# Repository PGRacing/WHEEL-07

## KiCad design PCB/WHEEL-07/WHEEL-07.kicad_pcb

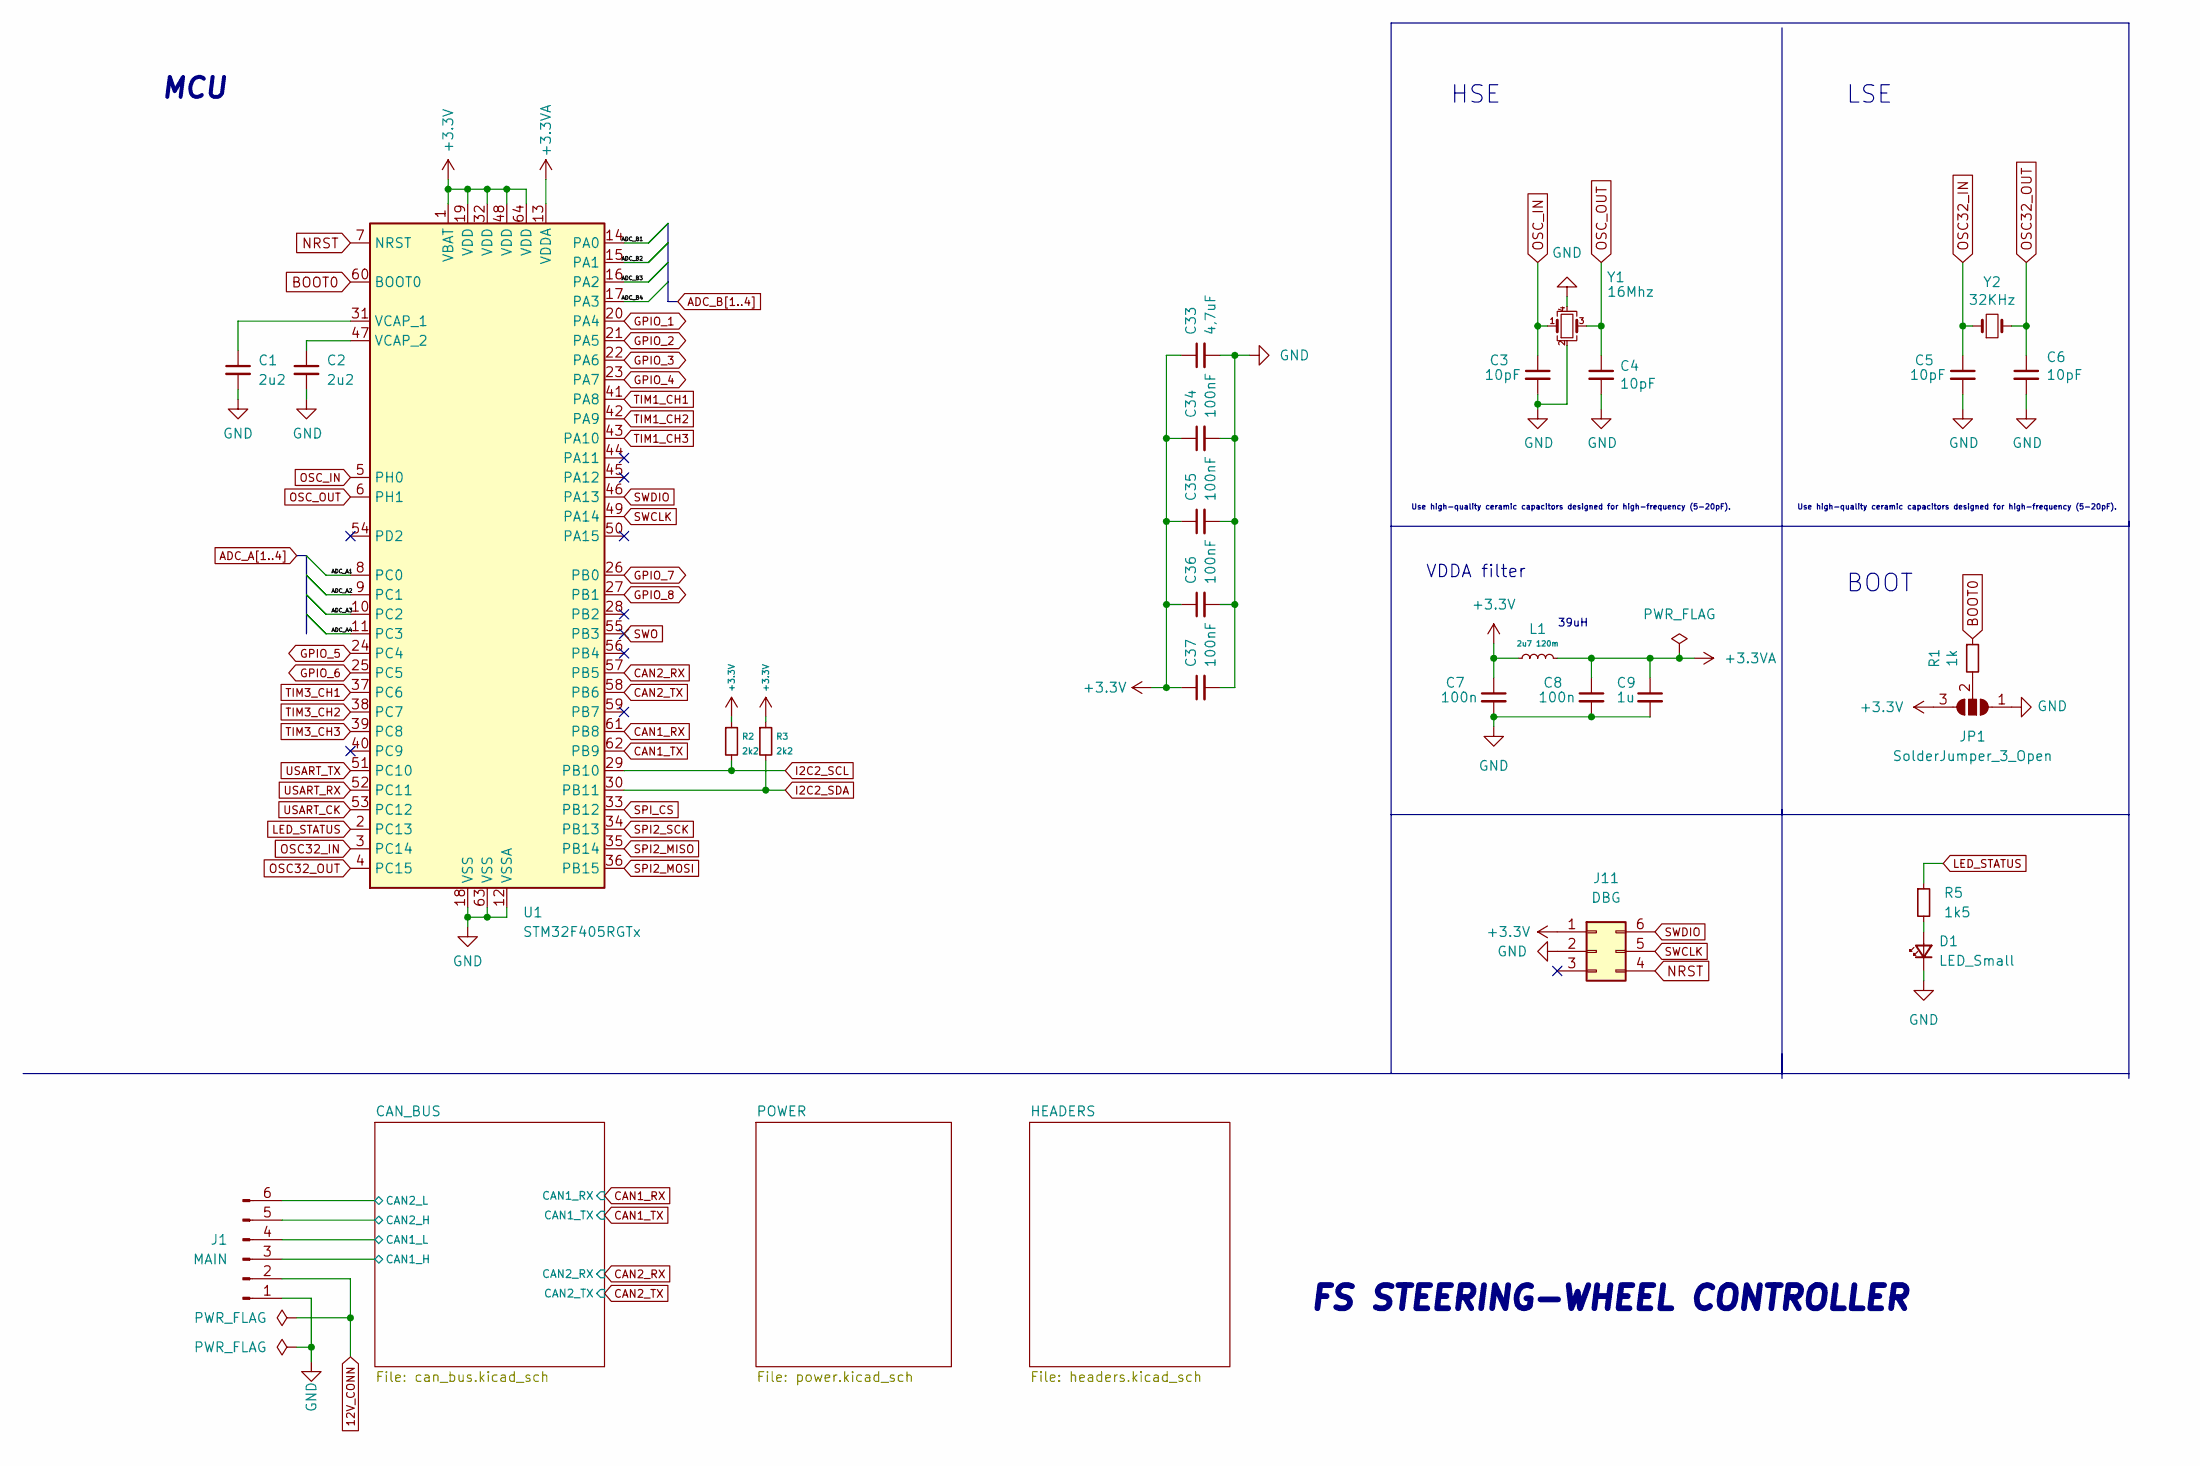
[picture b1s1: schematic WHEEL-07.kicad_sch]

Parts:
C1, C2: 2u2; C_0402_1005Metric_Pad0.74x0.62mm_HandSolder
C3, C4, C5, C6: 10pF; C_0402_1005Metric_Pad0.74x0.62mm_HandSolder
C7, C8: 100n; C_0402_1005Metric_Pad0.74x0.62mm_HandSolder
C9: 1u; C_0402_1005Metric_Pad0.74x0.62mm_HandSolder
C33: 4,7uF; C_0603_1608Metric
C34, C35, C36, C37: 100nF; C_0402_1005Metric_Pad0.74x0.62mm_HandSolder
D1: LED_Small; LED_0805_2012Metric
J1: MAIN; Molex_Micro-Latch_53254-0670_1x06_P2.00mm_Horizontal
J11: DBG; PinHeader_2x03_P1.27mm_Vertical
JP1: SolderJumper_3_Open; SolderJumper-3_P1.3mm_Open_RoundedPad1.0x1.5mm
L1: 2u7 120m; L_0402_1005Metric
R1: 1k; R_0402_1005Metric_Pad0.72x0.64mm_HandSolder
R2, R3: 2k2; R_0402_1005Metric_Pad0.72x0.64mm_HandSolder
R5: 1k5; R_0402_1005Metric_Pad0.72x0.64mm_HandSolder
U1: STM32F405RGTx; LQFP-64_10x10mm_P0.5mm
Y1: 16Mhz; Crystal_SMD_2016-4Pin_2.0x1.6mm
Y2: 32KHz; Crystal_SMD_3215-2Pin_3.2x1.5mm

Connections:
12V_CONN: J1.2; also elsewhere on the board
+3.3V: C7.1, C33.1, C34.1, C35.1, C36.1, C37.1, J11.1, JP1.3 (B), L1.1, R2.1, R3.1, U1.1 (VBAT), U1.19 (VDD), U1.32 (VDD), U1.48 (VDD), U1.64 (VDD); also elsewhere on the board
+3.3VA: C8.1, C9.1, L1.2, U1.13 (VDDA)
/CAN_BUS/CAN1_H: J1.3; also elsewhere on the board
/CAN_BUS/CAN1_L: J1.4; also elsewhere on the board
/CAN_BUS/CAN2_H: J1.5; also elsewhere on the board
/CAN_BUS/CAN2_L: J1.6; also elsewhere on the board
ADC_A1: U1.8 (PC0); also elsewhere on the board
ADC_A2: U1.9 (PC1); also elsewhere on the board
ADC_A3: U1.10 (PC2); also elsewhere on the board
ADC_A4: U1.11 (PC3); also elsewhere on the board
ADC_B1: U1.14 (PA0); also elsewhere on the board
ADC_B2: U1.15 (PA1); also elsewhere on the board
ADC_B3: U1.16 (PA2); also elsewhere on the board
ADC_B4: U1.17 (PA3); also elsewhere on the board
BOOT0: R1.1, U1.60 (BOOT0)
CAN1_RX: U1.61 (PB8); also elsewhere on the board
CAN1_TX: U1.62 (PB9); also elsewhere on the board
CAN2_RX: U1.57 (PB5); also elsewhere on the board
CAN2_TX: U1.58 (PB6); also elsewhere on the board
GND: C1.2, C2.2, C3.2, C4.2, C5.2, C6.2, C7.2, C8.2, C9.2, C33.2, C34.2, C35.2, C36.2, C37.2, D1.1 (K), J1.1, J11.2, JP1.1 (A), U1.12 (VSSA), U1.18 (VSS), U1.63 (VSS), Y1.2, Y1.4; also elsewhere on the board
GPIO_1: U1.20 (PA4); also elsewhere on the board
GPIO_2: U1.21 (PA5); also elsewhere on the board
GPIO_3: U1.22 (PA6); also elsewhere on the board
GPIO_4: U1.23 (PA7); also elsewhere on the board
GPIO_5: U1.24 (PC4); also elsewhere on the board
GPIO_6: U1.25 (PC5); also elsewhere on the board
GPIO_7: U1.26 (PB0); also elsewhere on the board
GPIO_8: U1.27 (PB1); also elsewhere on the board
I2C2_SCL: R2.2, U1.29 (PB10); also elsewhere on the board
I2C2_SDA: R3.2, U1.30 (PB11); also elsewhere on the board
LED_STATUS: R5.1, U1.2 (PC13)
NRST: J11.4, U1.7 (NRST)
unnamed: C1.1, U1.31 (VCAP_1)
unnamed: C2.1, U1.47 (VCAP_2)
unnamed: D1.2 (A), R5.2
unnamed: JP1.2 (C), R1.2
OSC32_IN: C5.1, U1.3 (PC14), Y2.1
OSC32_OUT: C6.1, U1.4 (PC15), Y2.2
OSC_IN: C3.1, U1.5 (PH0), Y1.1
OSC_OUT: C4.1, U1.6 (PH1), Y1.3
SPI2_MISO: U1.35 (PB14); also elsewhere on the board
SPI2_MOSI: U1.36 (PB15); also elsewhere on the board
SPI2_SCK: U1.34 (PB13); also elsewhere on the board
SPI_CS: U1.33 (PB12); also elsewhere on the board
SWCLK: J11.5, U1.49 (PA14)
SWDIO: J11.6, U1.46 (PA13)
SWO: U1.55 (PB3)
TIM1_CH1: U1.41 (PA8); also elsewhere on the board
TIM1_CH2: U1.42 (PA9); also elsewhere on the board
TIM1_CH3: U1.43 (PA10); also elsewhere on the board
TIM3_CH1: U1.37 (PC6); also elsewhere on the board
TIM3_CH2: U1.38 (PC7); also elsewhere on the board
TIM3_CH3: U1.39 (PC8); also elsewhere on the board
USART_CK: U1.53 (PC12)
USART_RX: U1.52 (PC11)
USART_TX: U1.51 (PC10)

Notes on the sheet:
39uH
LSE
MCU
BOOT
Use high-quality ceramic capacitors designed for high-frequency (5-20pF).
HSE
VDDA filter
FS STEERING-WHEEL CONTROLLER

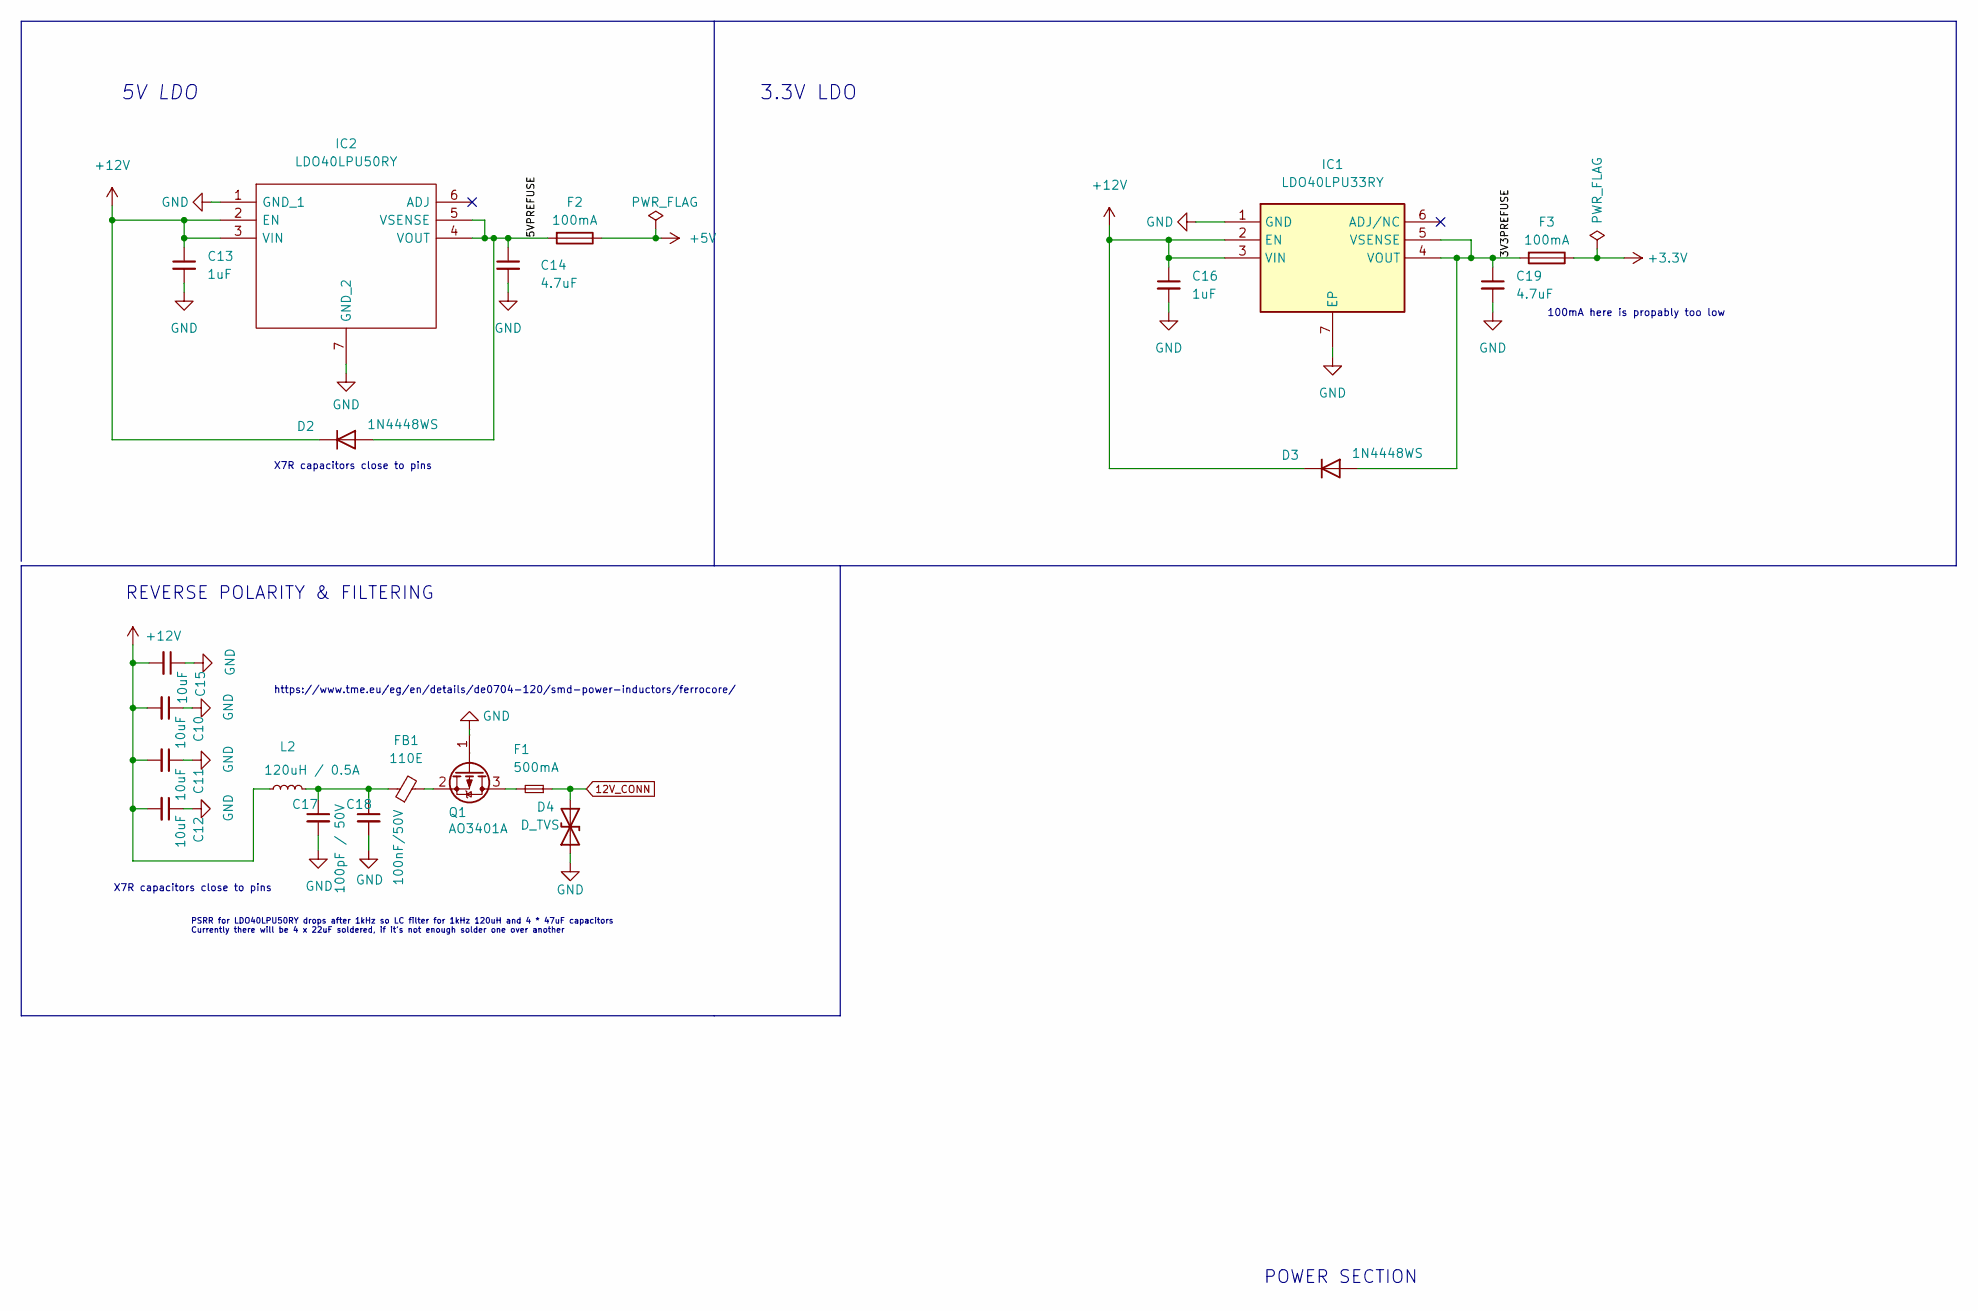
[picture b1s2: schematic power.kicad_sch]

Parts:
C10, C11, C12, C15: 10uF; C_1206_3216Metric
C13, C16: 1uF; C_0805_2012Metric
C14, C19: 4.7uF; C_0603_1608Metric
C17: 100pF / 50V; C_0402_1005Metric
C18: 100nF/50V; C_0402_1005Metric
D2, D3: 1N4448WS; D_SOD-323
D4: D_TVS; D_SMA
F1: 500mA; Fuse_0805_2012Metric
F2, F3: 100mA; Fuse_0805_2012Metric
FB1: 110E; LED_0805_2012Metric
IC1: LDO40LPU33RY; SON95P300X300X90-7N-D; Manufacturer_Part_Number LDO40LPU33RY; Mouser Part Number 511-LDO40LPU33RY
IC2: LDO40LPU50RY; SON95P300X300X90-7N-D; Manufacturer_Part_Number LDO40LPU50RY; Mouser Part Number 511-LDO40LPU50RY
L2: 120uH / 0.5A; L_7.3x7.3_H4.5
Q1: AO3401A; SOT-23

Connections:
12V_CONN: D4.2 (A2), F1.1; also elsewhere on the board
+3.3V: F3.1; also elsewhere on the board
+5V: F2.1; also elsewhere on the board
+12V: C10.2, C11.2, C12.2, C13.1, C15.2, C16.1, D2.1 (K), D3.1 (K), IC1.2 (EN), IC1.3 (VIN), IC2.2 (EN), IC2.3 (VIN), L2.1
/POWER/3V3PREFUSE: C19.1, D3.2 (A), F3.2, IC1.4 (VOUT), IC1.5 (VSENSE)
/POWER/5VPREFUSE: C14.1, D2.2 (A), F2.2, IC2.4 (VOUT), IC2.5 (VSENSE)
GND: C10.1, C11.1, C12.1, C13.2, C14.2, C15.1, C16.2, C17.2, C18.2, C19.2, D4.1 (A1), IC1.1 (GND), IC1.7 (EP), IC2.1 (GND_1), IC2.7 (GND_2), Q1.1 (G); also elsewhere on the board
unnamed: C17.1, C18.1, FB1.1, L2.2
unnamed: F1.2, Q1.3 (D)
unnamed: FB1.2, Q1.2 (S)

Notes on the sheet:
X7R capacitors close to pins
POWER SECTION
100mA here is propably too low
PSRR for LDO40LPU50RY drops after 1kHz so LC filter for 1kHz 120uH and 4 * 47uF capacitors Currently there will be 4 x 22uF soldered, if it's not enough solder one over another
https://www.tme.eu/eg/en/details/de0704-120/smd-power-inductors/ferrocore/
3.3V LDO
5V LDO
REVERSE POLARITY & FILTERING

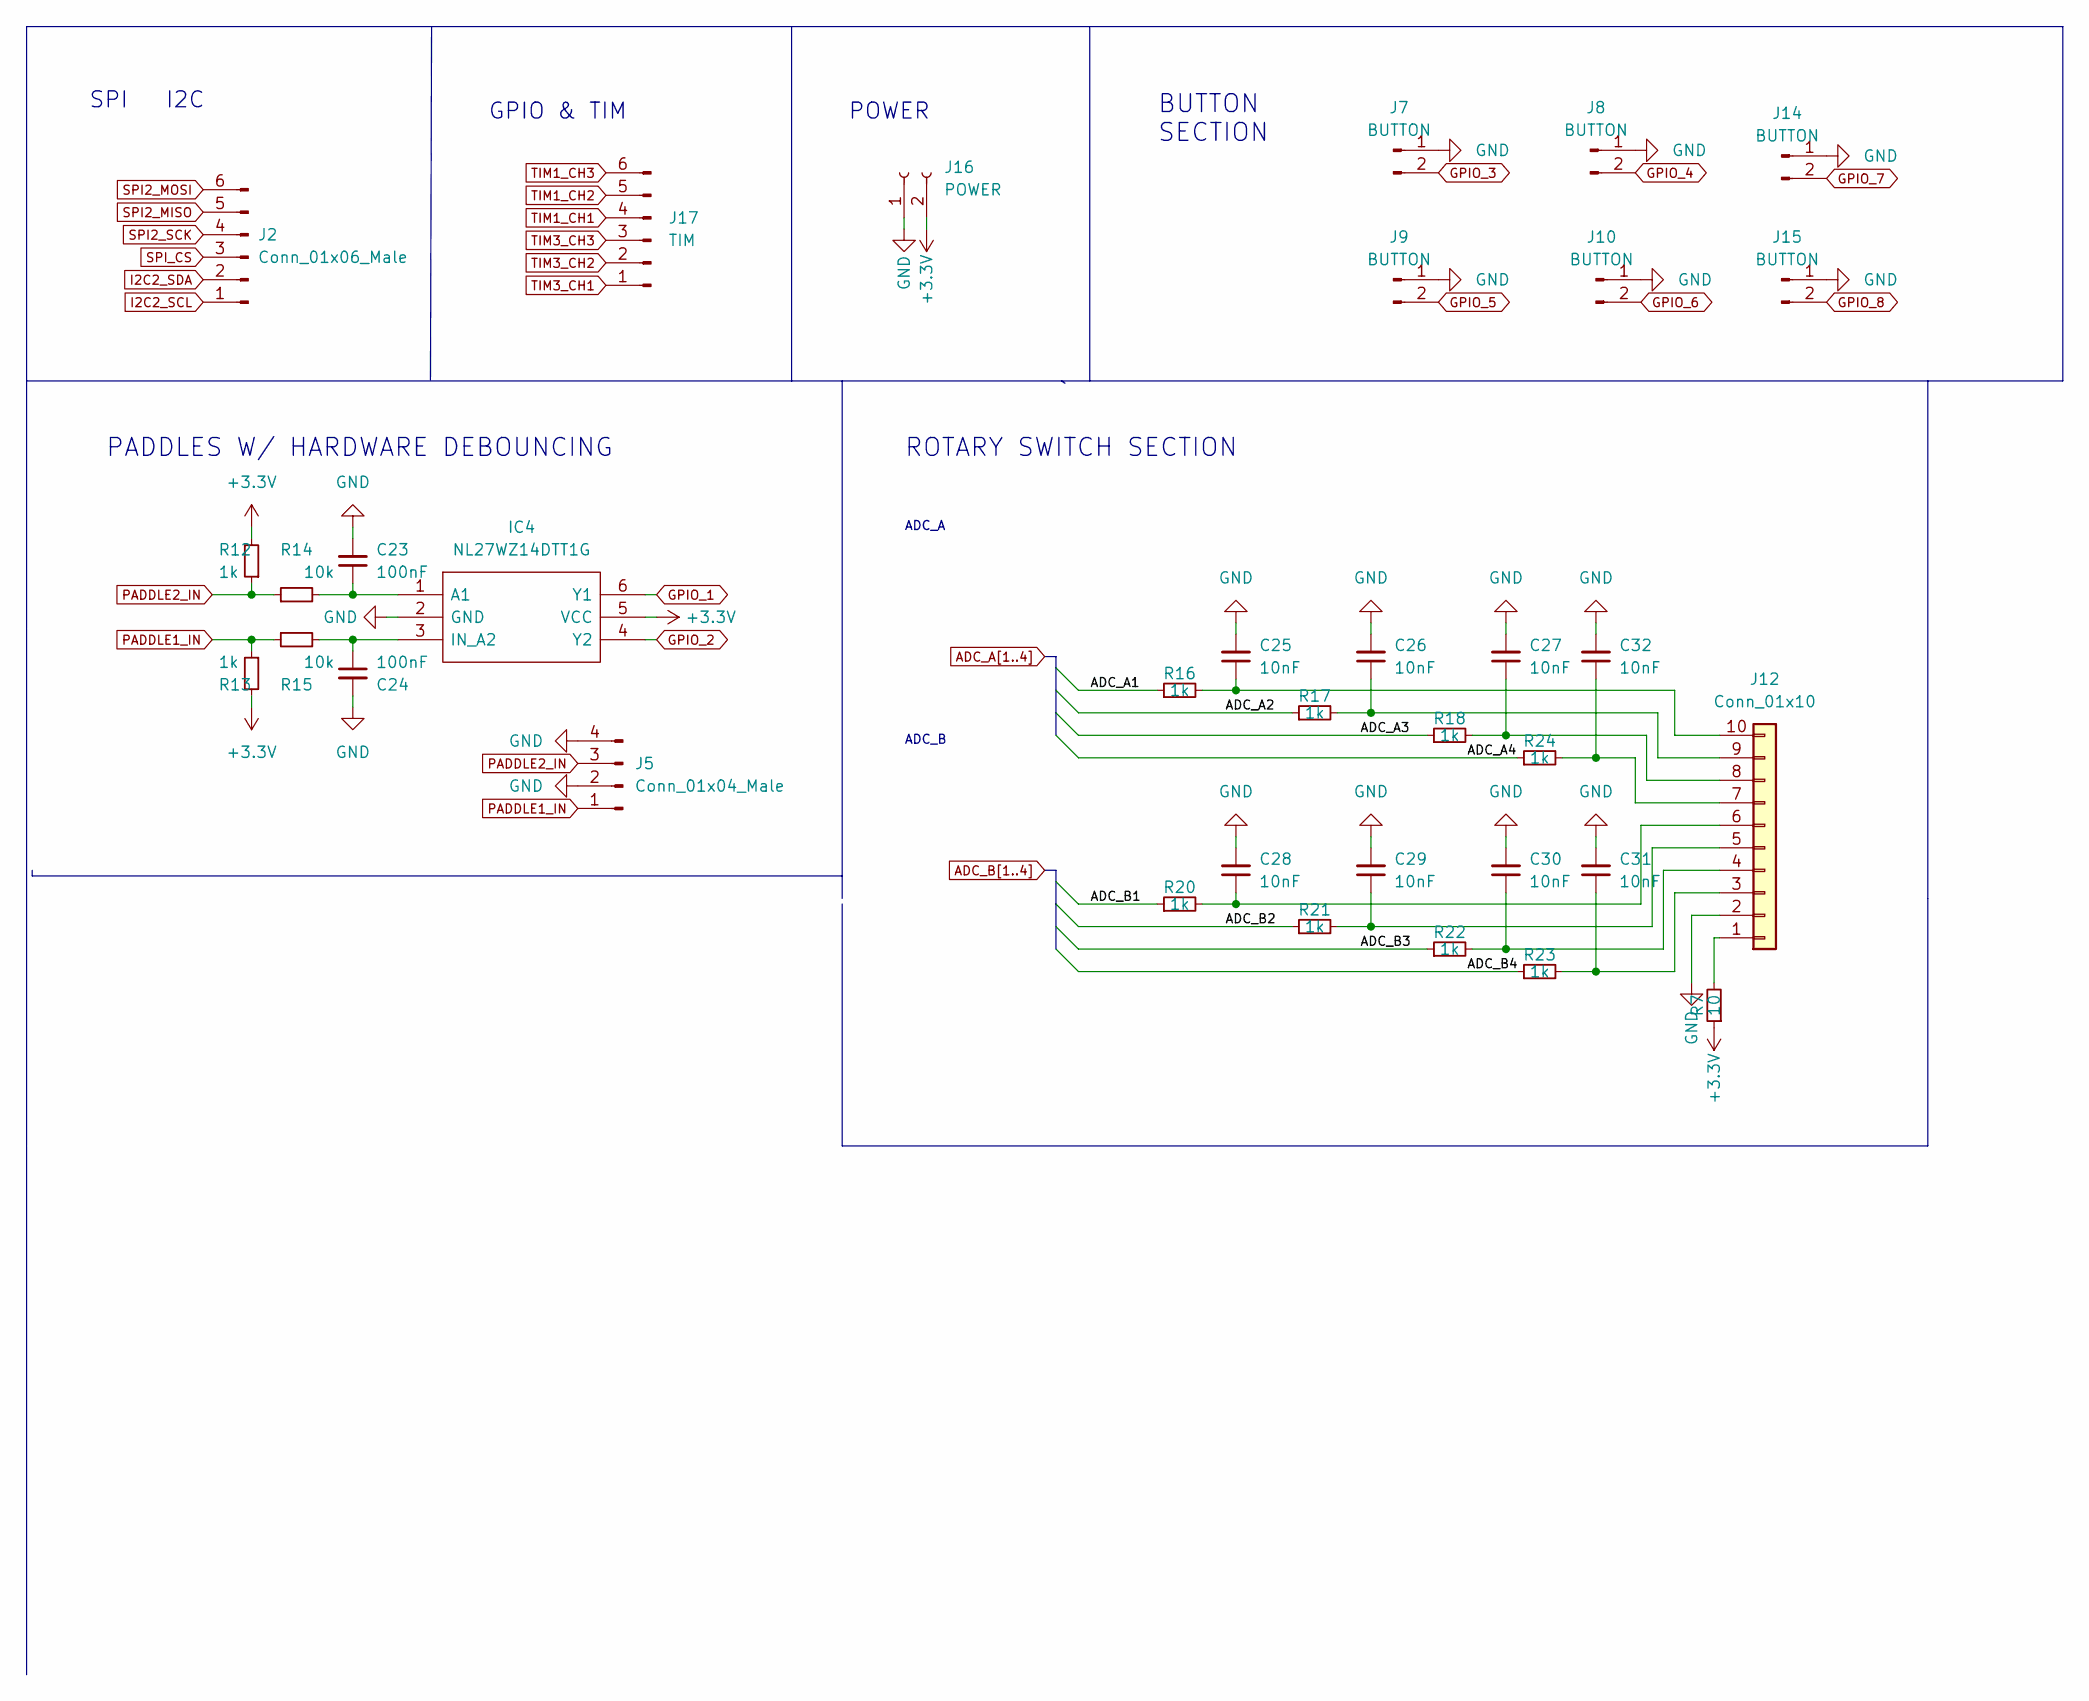
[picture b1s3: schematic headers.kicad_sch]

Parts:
C23, C24: 100nF; C_0402_1005Metric_Pad0.74x0.62mm_HandSolder
C25, C26, C27, C28, C29, C30, C31, C32: 10nF; C_0402_1005Metric_Pad0.74x0.62mm_HandSolder
IC4: NL27WZ14DTT1G; SOT95P275X110-6N; Manufacturer_Part_Number NL27WZ14DTT1G; Mouser Part Number 863-NL27WZ14DTT1G
J2: Conn_01x06_Male; PinHeader_1x06_P1.27mm_Vertical
J5: Conn_01x04_Male; Molex_Micro-Latch_53254-0470_1x04_P2.00mm_Horizontal
J7, J8, J9, J10, J14, J15: BUTTON; Molex_PicoBlade_53047-0210_1x02_P1.25mm_Vertical
J12: Conn_01x10; Molex_PicoBlade_53047-1010_1x10_P1.25mm_Vertical
J16: POWER; PinHeader_1x02_P2.54mm_Vertical
J17: TIM; Molex_PicoBlade_53047-0610_1x06_P1.25mm_Vertical
R7: 10; R_0805_2012Metric
R12, R13, R16, R17, R18, R20, R21, R22, R23, R24: 1k; R_0402_1005Metric_Pad0.72x0.64mm_HandSolder
R14, R15: 10k; R_0402_1005Metric_Pad0.72x0.64mm_HandSolder

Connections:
+3.3V: IC4.5 (VCC), J16.2, R7.1, R12.2, R13.2; also elsewhere on the board
ADC_A1: R16.1; also elsewhere on the board
ADC_A2: R17.1; also elsewhere on the board
ADC_A3: R18.1; also elsewhere on the board
ADC_A4: R24.1; also elsewhere on the board
ADC_B1: R20.1; also elsewhere on the board
ADC_B2: R21.1; also elsewhere on the board
ADC_B3: R22.1; also elsewhere on the board
ADC_B4: R23.1; also elsewhere on the board
GND: C23.2, C24.2, C25.2, C26.2, C27.2, C28.2, C29.2, C30.2, C31.2, C32.2, IC4.2 (GND), J5.2, J5.4, J7.1, J8.1, J9.1, J10.1, J12.2, J14.1, J15.1, J16.1; also elsewhere on the board
GPIO_1: IC4.6 (Y1); also elsewhere on the board
GPIO_2: IC4.4 (Y2); also elsewhere on the board
GPIO_3: J7.2; also elsewhere on the board
GPIO_4: J8.2; also elsewhere on the board
GPIO_5: J9.2; also elsewhere on the board
GPIO_6: J10.2; also elsewhere on the board
GPIO_7: J14.2; also elsewhere on the board
GPIO_8: J15.2; also elsewhere on the board
I2C2_SCL: J2.1; also elsewhere on the board
I2C2_SDA: J2.2; also elsewhere on the board
unnamed: C23.1, IC4.1 (A1), R14.2
unnamed: C24.1, IC4.3 (IN_A2), R15.2
unnamed: C25.1, J12.10, R16.2
unnamed: C26.1, J12.9, R17.2
unnamed: C27.1, J12.8, R18.2
unnamed: C28.1, J12.6, R20.2
unnamed: C29.1, J12.5, R21.2
unnamed: C30.1, J12.4, R22.2
unnamed: C31.1, J12.3, R23.2
unnamed: C32.1, J12.7, R24.2
unnamed: J12.1, R7.2
PADDLE1_IN: J5.1, R13.1, R15.1
PADDLE2_IN: J5.3, R12.1, R14.1
SPI2_MISO: J2.5; also elsewhere on the board
SPI2_MOSI: J2.6; also elsewhere on the board
SPI2_SCK: J2.4; also elsewhere on the board
SPI_CS: J2.3; also elsewhere on the board
TIM1_CH1: J17.4; also elsewhere on the board
TIM1_CH2: J17.5; also elsewhere on the board
TIM1_CH3: J17.6; also elsewhere on the board
TIM3_CH1: J17.1; also elsewhere on the board
TIM3_CH2: J17.2; also elsewhere on the board
TIM3_CH3: J17.3; also elsewhere on the board

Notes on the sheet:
POWER
BUTTON SECTION
ADC_A
PADDLES W/ HARDWARE DEBOUNCING
ROTARY SWITCH SECTION
ADC_B
GPIO & TIM
I2C
SPI

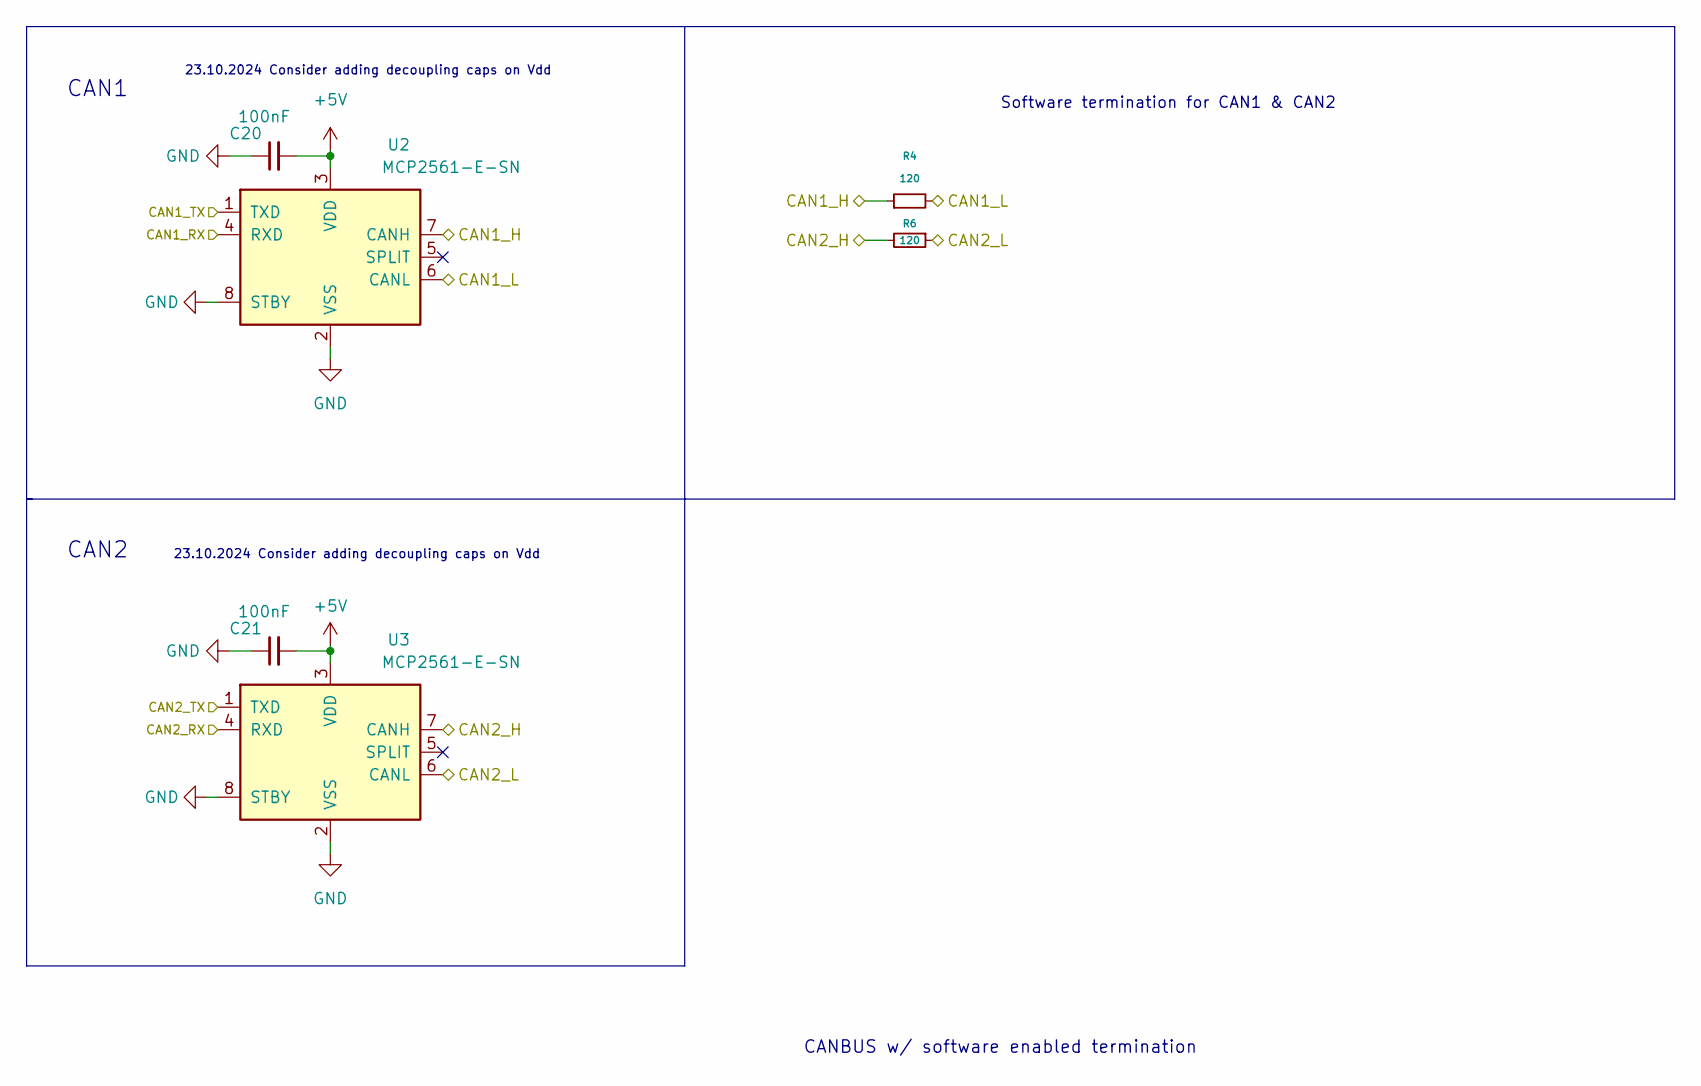
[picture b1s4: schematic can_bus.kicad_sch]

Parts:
C20, C21: 100nF; C_0402_1005Metric_Pad0.74x0.62mm_HandSolder
R4, R6: 120; R_0402_1005Metric_Pad0.72x0.64mm_HandSolder
U2, U3: MCP2561-E-SN; SOIC-8_3.9x4.9mm_P1.27mm

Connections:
+5V: C20.2, C21.2, U2.3 (VDD), U3.3 (VDD); also elsewhere on the board
/CAN_BUS/CAN1_H: R4.1, U2.7 (CANH); also elsewhere on the board
/CAN_BUS/CAN1_L: R4.2, U2.6 (CANL); also elsewhere on the board
/CAN_BUS/CAN2_H: R6.2, U3.7 (CANH); also elsewhere on the board
/CAN_BUS/CAN2_L: R6.1, U3.6 (CANL); also elsewhere on the board
CAN1_RX: U2.4 (RXD); also elsewhere on the board
CAN1_TX: U2.1 (TXD); also elsewhere on the board
CAN2_RX: U3.4 (RXD); also elsewhere on the board
CAN2_TX: U3.1 (TXD); also elsewhere on the board
GND: C20.1, C21.1, U2.2 (VSS), U2.8 (STBY), U3.2 (VSS), U3.8 (STBY); also elsewhere on the board

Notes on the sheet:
Software termination for CAN1 & CAN2
CANBUS w/ software enabled termination
CAN1
CAN2
23.10.2024 Consider adding decoupling caps on Vdd

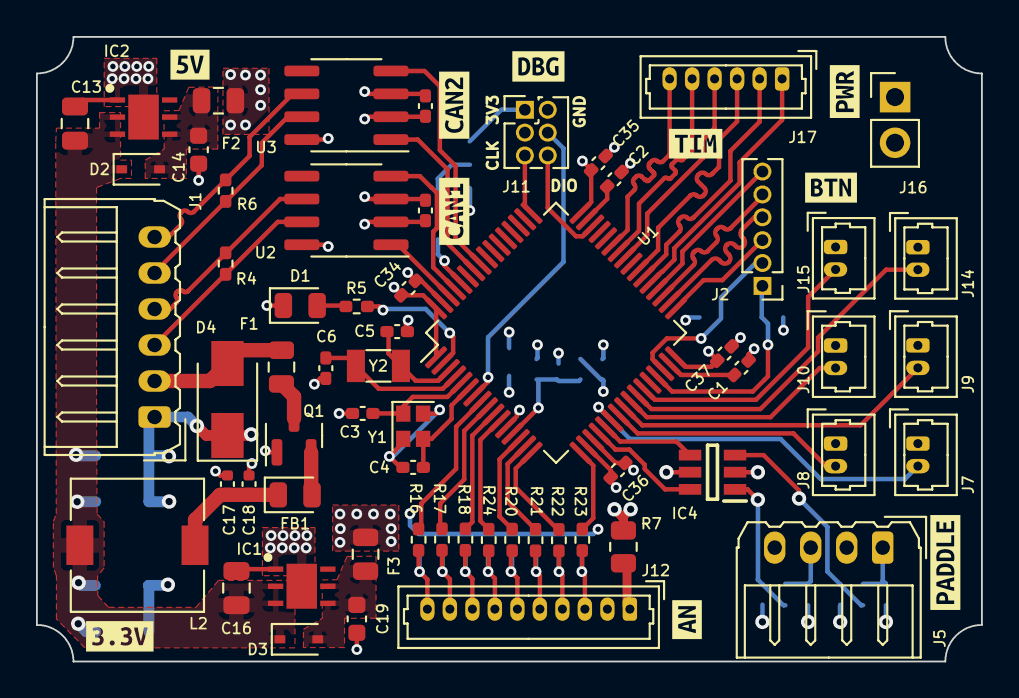
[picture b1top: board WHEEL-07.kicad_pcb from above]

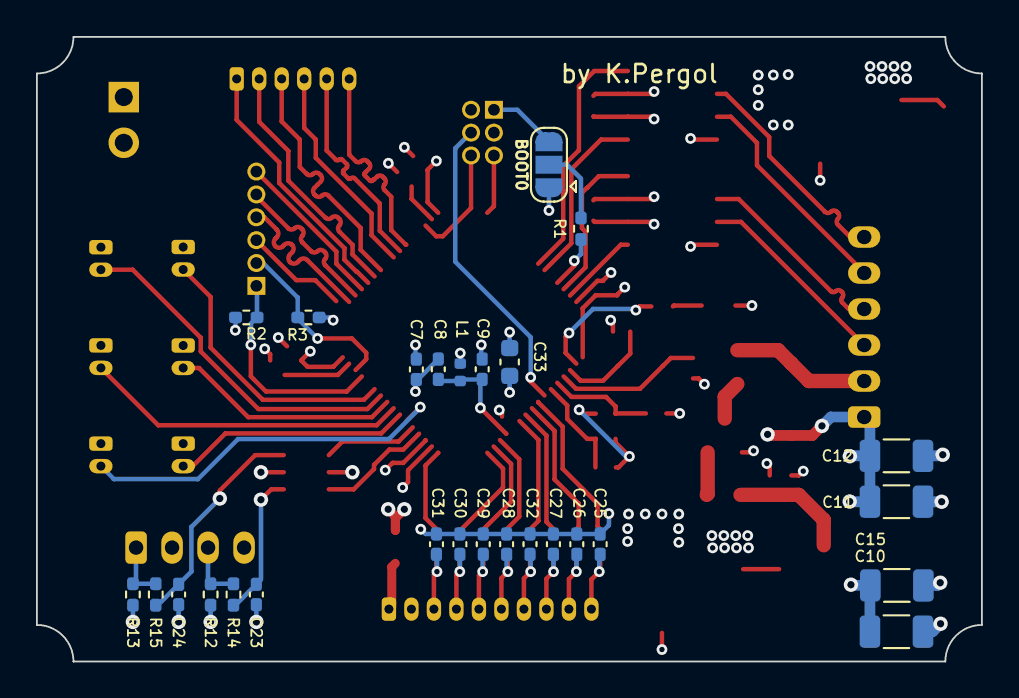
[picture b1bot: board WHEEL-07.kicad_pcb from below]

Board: 4 copper layers, 52.5 x 34.7 mm, 98 parts (27 on the bottom side), 73 nets.

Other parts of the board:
kibuzzard-6414F4C6: G***; kibuzzard-6414F4C6
kibuzzard-64076DC9: G***; kibuzzard-64076DC9
kibuzzard-64076DD2: G***; kibuzzard-64076DD2
kibuzzard-64076DF0: G***; kibuzzard-64076DF0
kibuzzard-64076DFA: G***; kibuzzard-64076DFA
kibuzzard-64076E40: G***; kibuzzard-64076E40
kibuzzard-64076F6A: G***; kibuzzard-64076F6A
kibuzzard-64135F75: G***; kibuzzard-64135F75
kibuzzard-64135F81: G***; kibuzzard-64135F81
kibuzzard-64137017: G***; kibuzzard-64137017

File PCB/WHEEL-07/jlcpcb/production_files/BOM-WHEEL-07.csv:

Comment;Designator;Footprint;LCSC
10;R7;R_0805_2012Metric;
100mA;F3;Fuse_0805_2012Metric;C2649565
100mA;F2;Fuse_0805_2012Metric;C2649565
100n;C8;C_0402_1005Metric_Pad0.74x0.62mm_HandSolder;C1525
100n;C7;C_0402_1005Metric_Pad0.74x0.62mm_HandSolder;C1525
100nF;C21;C_0402_1005Metric_Pad0.74x0.62mm_HandSolder;C1525
100nF;C20;C_0402_1005Metric_Pad0.74x0.62mm_HandSolder;C1525
100nF;C35;C_0402_1005Metric_Pad0.74x0.62mm_HandSolder;C1525
100nF;C37;C_0402_1005Metric_Pad0.74x0.62mm_HandSolder;C1525
100nF;C36;C_0402_1005Metric_Pad0.74x0.62mm_HandSolder;C1525
100nF;C34;C_0402_1005Metric_Pad0.74x0.62mm_HandSolder;C1525
100nF;C23;C_0402_1005Metric_Pad0.74x0.62mm_HandSolder;C1525
100nF;C24;C_0402_1005Metric_Pad0.74x0.62mm_HandSolder;C1525
100nF/50V;C18;C_0402_1005Metric;C307331
100pF / 50V;C17;C_0402_1005Metric;C307331
10k;R15;R_0402_1005Metric_Pad0.72x0.64mm_HandSolder;
10k;R14;R_0402_1005Metric_Pad0.72x0.64mm_HandSolder;
10nF;C27;C_0402_1005Metric_Pad0.74x0.62mm_HandSolder;
10nF;C32;C_0402_1005Metric_Pad0.74x0.62mm_HandSolder;
10nF;C30;C_0402_1005Metric_Pad0.74x0.62mm_HandSolder;
10nF;C26;C_0402_1005Metric_Pad0.74x0.62mm_HandSolder;
10nF;C28;C_0402_1005Metric_Pad0.74x0.62mm_HandSolder;
10nF;C31;C_0402_1005Metric_Pad0.74x0.62mm_HandSolder;
10nF;C29;C_0402_1005Metric_Pad0.74x0.62mm_HandSolder;
10nF;C25;C_0402_1005Metric_Pad0.74x0.62mm_HandSolder;
10pF;C4;C_0402_1005Metric_Pad0.74x0.62mm_HandSolder;
10pF;C6;C_0402_1005Metric_Pad0.74x0.62mm_HandSolder;
10pF;C5;C_0402_1005Metric_Pad0.74x0.62mm_HandSolder;
10pF;C3;C_0402_1005Metric_Pad0.74x0.62mm_HandSolder;
10uF;C12;C_1206_3216Metric;
10uF;C10;C_1206_3216Metric;
10uF;C15;C_1206_3216Metric;
10uF;C11;C_1206_3216Metric;
110E;FB1;LED_0805_2012Metric;C1015
120;R6;R_0402_1005Metric_Pad0.72x0.64mm_HandSolder;C25079
120;R4;R_0402_1005Metric_Pad0.72x0.64mm_HandSolder;C25079
120uH / 0.5A;L2;L_7.3x7.3_H4.5;C5339531
16Mhz;Y1;Crystal_SMD_2016-4Pin_2.0x1.6mm;C7294751
1k;R18;R_0402_1005Metric_Pad0.72x0.64mm_HandSolder;C11702
1k;R16;R_0402_1005Metric_Pad0.72x0.64mm_HandSolder;C11702
1k;R24;R_0402_1005Metric_Pad0.72x0.64mm_HandSolder;C11702
1k;R22;R_0402_1005Metric_Pad0.72x0.64mm_HandSolder;C11702
1k;R17;R_0402_1005Metric_Pad0.72x0.64mm_HandSolder;C11702
1k;R21;R_0402_1005Metric_Pad0.72x0.64mm_HandSolder;C11702
1k;R20;R_0402_1005Metric_Pad0.72x0.64mm_HandSolder;C11702
1k;R23;R_0402_1005Metric_Pad0.72x0.64mm_HandSolder;C11702
1k;R13;R_0402_1005Metric_Pad0.72x0.64mm_HandSolder;C11702
1k;R12;R_0402_1005Metric_Pad0.72x0.64mm_HandSolder;C11702
1k;R1;R_0402_1005Metric_Pad0.72x0.64mm_HandSolder;C11702
1k5;R5;R_0402_1005Metric_Pad0.72x0.64mm_HandSolder;
1N4448WS;D2;D_SOD-323;C167101
1N4448WS;D3;D_SOD-323;C167101
1u;C9;C_0402_1005Metric_Pad0.74x0.62mm_HandSolder;C28323
1uF;C13;C_0805_2012Metric;C28323
1uF;C16;C_0805_2012Metric;C28323
2k2;R2;R_0402_1005Metric_Pad0.72x0.64mm_HandSolder;
2k2;R3;R_0402_1005Metric_Pad0.72x0.64mm_HandSolder;
2u2;C1;C_0402_1005Metric_Pad0.74x0.62mm_HandSolder;C12530
2u2;C2;C_0402_1005Metric_Pad0.74x0.62mm_HandSolder;C12530
2u7 120m;L1;L_0402_1005Metric;
32KHz;Y2;Crystal_SMD_3215-2Pin_3.2x1.5mm;
4;7uF;C33;C_0603_1608Metric
4.7uF;C14;C_0603_1608Metric;
4.7uF;C19;C_0603_1608Metric;
500mA;F1;Fuse_0805_2012Metric;
AO3401A;Q1;SOT-23;C15127
BUTTON;J7;Molex_PicoBlade_53047-0210_1x02_P1.25mm_Vertical;C114130
BUTTON;J14;Molex_PicoBlade_53047-0210_1x02_P1.25mm_Vertical;C114130
BUTTON;J10;Molex_PicoBlade_53047-0210_1x02_P1.25mm_Vertical;C114130
BUTTON;J8;Molex_PicoBlade_53047-0210_1x02_P1.25mm_Vertical;C114130
BUTTON;J9;Molex_PicoBlade_53047-0210_1x02_P1.25mm_Vertical;C114130
BUTTON;J15;Molex_PicoBlade_53047-0210_1x02_P1.25mm_Vertical;C114130
Conn_01x04_Male;J5;Molex_Micro-Latch_53254-0470_1x04_P2.00mm_Horizontal;C293629
Conn_01x06_Male;J2;PinHeader_1x06_P1.27mm_Vertical;
Conn_01x06_Male;J1;Molex_Micro-Latch_53254-0670_1x06_P2.00mm_Horizontal;C585951
Conn_01x10;J12;Molex_PicoBlade_53047-1010_1x10_P1.25mm_Vertical;C505021
D_TVS;D4;D_SMA;C1509532
DBG;J11;PinHeader_2x03_P1.27mm_Vertical;
LDO40LPU33RY;IC1;SON95P300X300X90-7N-D;
LDO40LPU50RY;IC2;SON95P300X300X90-7N-D;
LED_Small;D1;LED_0805_2012Metric;C84256
MCP2561-E-SN;U2;SOIC-8_3.9x4.9mm_P1.27mm;C219833
MCP2561-E-SN;U3;SOIC-8_3.9x4.9mm_P1.27mm;C219833
NL27WZ14DTT1G;IC4;SOT95P275X110-6N;C233559
POWER;J16;PinHeader_1x02_P2.54mm_Vertical;
SolderJumper_3_Open;JP1;SolderJumper-3_P1.3mm_Open_RoundedPad1.0x1.5mm;
STM32F405RGTx;U1;LQFP-64_10x10mm_P0.5mm;C1337199
TIM;J17;Molex_PicoBlade_53047-0610_1x06_P1.25mm_Vertical;

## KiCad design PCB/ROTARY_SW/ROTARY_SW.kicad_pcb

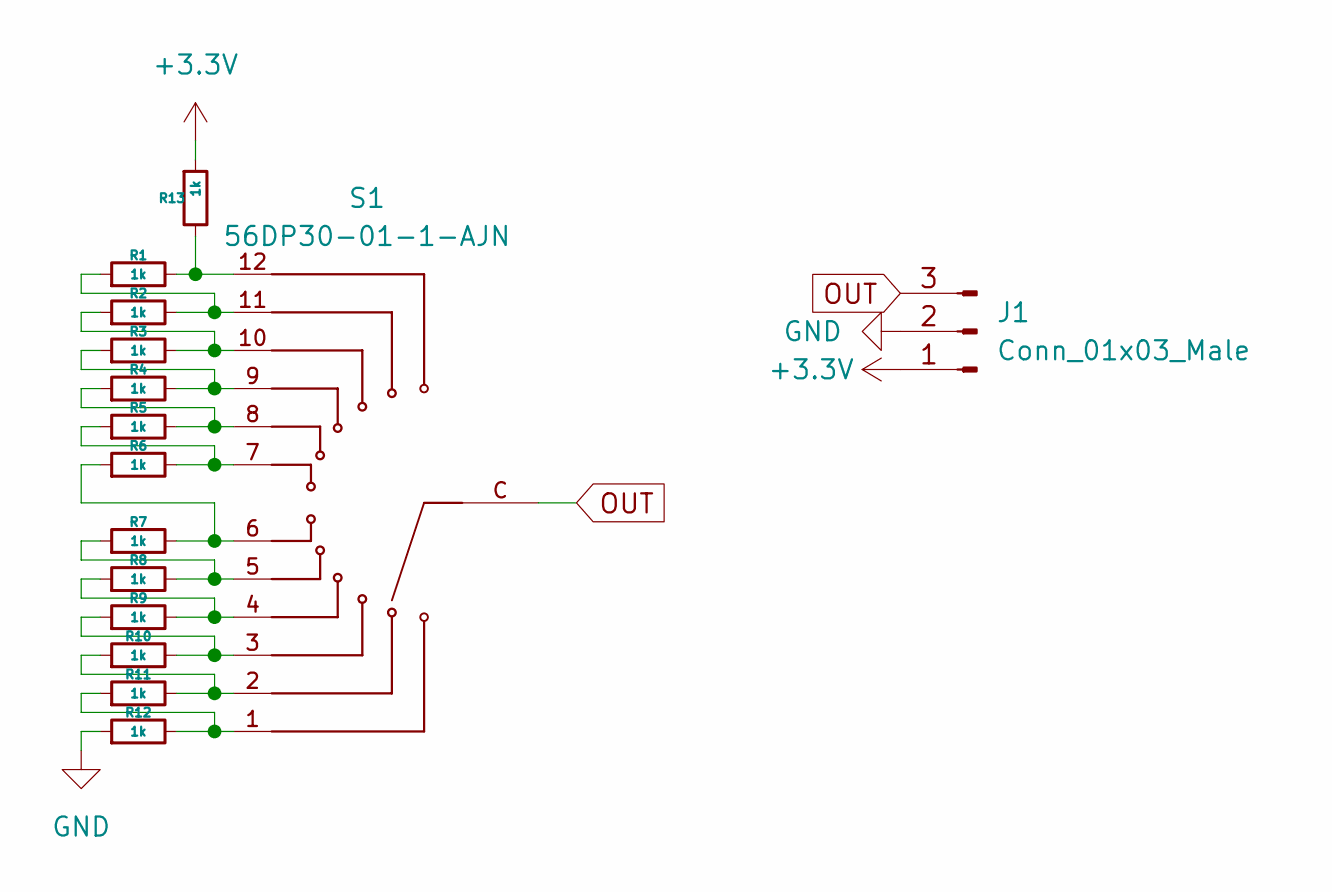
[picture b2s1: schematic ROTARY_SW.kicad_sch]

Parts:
J1: Conn_01x03_Male; PinHeader_1x03_P1.27mm_Vertical
R1, R2, R3, R4, R5, R6, R7, R8, R9, R10, R11, R12, R13: 1k; R_0402_1005Metric
S1: 56DP30-01-1-AJN; SW_56DP30-01-1-AJN; PARTREV 04/14

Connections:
+3.3V: J1.1, R13.1
GND: J1.2, R12.1
unnamed: R1.1, R2.2, S1.11
unnamed: R1.2, R13.2, S1.12
unnamed: R2.1, R3.2, S1.10
unnamed: R3.1, R4.2, S1.9
unnamed: R4.1, R5.2, S1.8
unnamed: R5.1, R6.2, S1.7
unnamed: R6.1, R7.2, S1.6
unnamed: R7.1, R8.2, S1.5
unnamed: R8.1, R9.2, S1.4
unnamed: R10.1, R11.2, S1.2
unnamed: R9.1, R10.2, S1.3
unnamed: R11.1, R12.2, S1.1
OUT: J1.3, S1.C

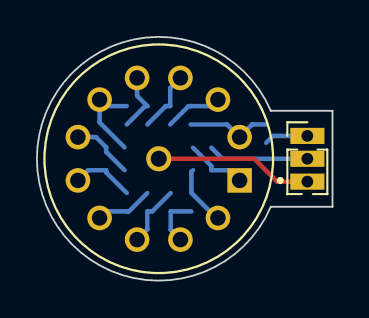
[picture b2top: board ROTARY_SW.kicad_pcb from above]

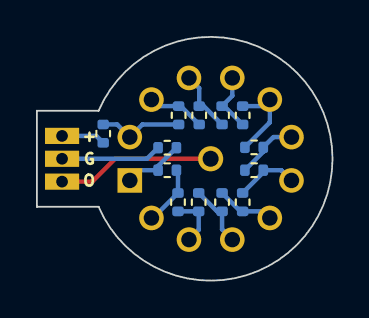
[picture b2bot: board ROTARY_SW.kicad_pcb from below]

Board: 2 copper layers, 16.4 x 13.5 mm, 15 parts (13 on the bottom side), 15 nets.
